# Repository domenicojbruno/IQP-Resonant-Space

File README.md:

# IQP-Resonant-Space

An interactive "resonant wall" for a hallway. VL53L0X time-of-flight sensors detect when people cross a threshold, and a honeycomb of 13 hexagonal panels, each moved by a linear actuator, pulls back from and pushes out toward them. Each actuator is driven by a BTS7960 H-bridge, and three ESP32-WROOM-32 boards each drive one row of the wall.

## System at a glance

- **Wall:** 13 motors in a flat-top hex honeycomb: 5 on top (Board A), 3 in the middle (Board B) and 5 on the bottom (Board C).
- **Motor boards:** ESP32-WROOM-32 + up to 5 BTS7960 H-bridges each, with limit switches per actuator. Position is time-based, since the actuators have no encoders.
- **Sensing:** 4× VL53L0X ToF sensors for hallway occupancy. Two overhead cameras for hand tracking are planned.
- **Master:** a PC app (Python/Tkinter) talks to the boards over **ESP-NOW** through a USB-connected ESP32 gateway. This replaced the original serial-link plan.

## Repository layout

| Path | Contents |
|---|---|
| [`firmware/ResonantWallMotorBoard/`](firmware/ResonantWallMotorBoard/) | Motor board sketch (one image for all three boards): BTS7960 drive, limit switches, time-based position, HOME/CAL/GOTO, ESP-NOW link and USB bench console |
| [`firmware/ResonantWallGateway/`](firmware/ResonantWallGateway/) | USB-serial ↔ ESP-NOW gateway sketch for the ESP32 that stays plugged into the PC |
| [`master/`](master/) | PC master app `resonant_wall_master.py` (Python/Tkinter + pyserial): wall view, threshold and GOTO-stream control, per-board links, E-STOP |
| [`docs/resonant-wall-master-spec.md`](docs/resonant-wall-master-spec.md) | Wall topology, motor addressing, actuation model and command semantics |
| [`docs/motor-board-peripheral-firmware.md`](docs/motor-board-peripheral-firmware.md) | Motor board firmware notes: ESP-NOW transport, pinout, open items |
| [`docs/master-ui-and-gateway.md`](docs/master-ui-and-gateway.md) | PC master app and ESP-NOW gateway: packet formats, line protocol, control logic |
| [`docs/vl53l0x-arduino-uno-test.md`](docs/vl53l0x-arduino-uno-test.md) | VL53L0X range test on an Arduino Uno: wiring, findings, ESP32 porting notes |
| [`docs/hexagon-node-controller.html`](docs/hexagon-node-controller.html) | Earlier node controller design sheet (Rev B): power, pin map, H-bridge wiring, sensors, BOM, layout rules |
| [`simulator/index.html`](simulator/index.html) | Resonant Wall master-node simulator. Open it in a browser and move the cursor over the hex field to see per-motor commands |
| [`docs/images/TOFpins.png`](docs/images/TOFpins.png) | VL53L0X breakout pinout |
| [`hardware/motor-driver-board/`](hardware/motor-driver-board/) | KiCad PCB (`.kicad_pcb`) and schematic PDF for the motor driver board |
| [`datasheets/`](datasheets/) | ESP32-WROOM-32, VL53L0X, BTS7960 and Arduino Uno (A000066) datasheets |

## Getting started

1. **Gateway.** Flash `firmware/ResonantWallGateway/` to a spare ESP32 and plug it into the PC. It prints `MAC <mac>` at boot.
2. **Motor boards.** In `firmware/ResonantWallMotorBoard/config.h`, set `BOARD_ID` / `MOTOR_COUNT` (0/5, 1/3, 2/5 for rows A/B/C), `USE_OLD_BENCH_PINOUT`, and `MASTER_MAC` (the gateway's MAC). Then flash each board. Each board prints its own MAC over USB at boot. The board needs Arduino-ESP32 core 3.x; the gateway builds on core 2.x or 3.x.
3. **Master.** `pip install -r master/requirements.txt`, then `python3 master/resonant_wall_master.py`. Choose the gateway port and enter each board's MAC (the app also learns a MAC from the board's first status packet). Pick a mode: Manual, Threshold (FWD/REV) or GOTO stream. Esc is E-STOP. Settings are saved to `master/resonant_wall_master.json` on exit.
4. Run `CAL` once per motor (MotorDriver Board only; it needs limit switches) so time-based positions and GOTO use the measured travel time.

## Protocol summary

| Packet | Bytes |
|---|---|
| Command (master → board) | `[0xA5, motorIdx, cmd, value]`, where `motorIdx 0xFF` means all motors |
| Status (board → master, every 250 ms) | `[0xA6, boardId, motorIdx, state, posPct, fault]` |

Command codes: FWD 0 · REV 1 · STOP 2 · HOME 3 · CAL 4 · GOTO 5. See [`docs/master-ui-and-gateway.md`](docs/master-ui-and-gateway.md) for the full tables.

## Status

- The motor driver board has been designed in KiCad but not yet fabricated. Its pinout is transcribed from the schematic and still needs to be verified against hardware.
- The VL53L0X has been bench-tested on an Arduino Uno.
- The master-node simulator (`simulator/`) runs as-is in any browser.
- The firmware and master app source is now in `firmware/` and `master/`, written from the specs in `docs/`. Neither sketch has been compiled against a real ESP32 core or run on hardware yet. Both were compiled on a host with stub headers. The motor board state machine was exercised against a simulated actuator, and the master app was tested against fake boards and a fake gateway on virtual serial ports.
- `vl53l0x_distance_test.ino` (the Uno sensor test) is not in this repo yet, and ToF occupancy is not wired into the master. The "Hallway occupied" toggle in the app stands in for it.

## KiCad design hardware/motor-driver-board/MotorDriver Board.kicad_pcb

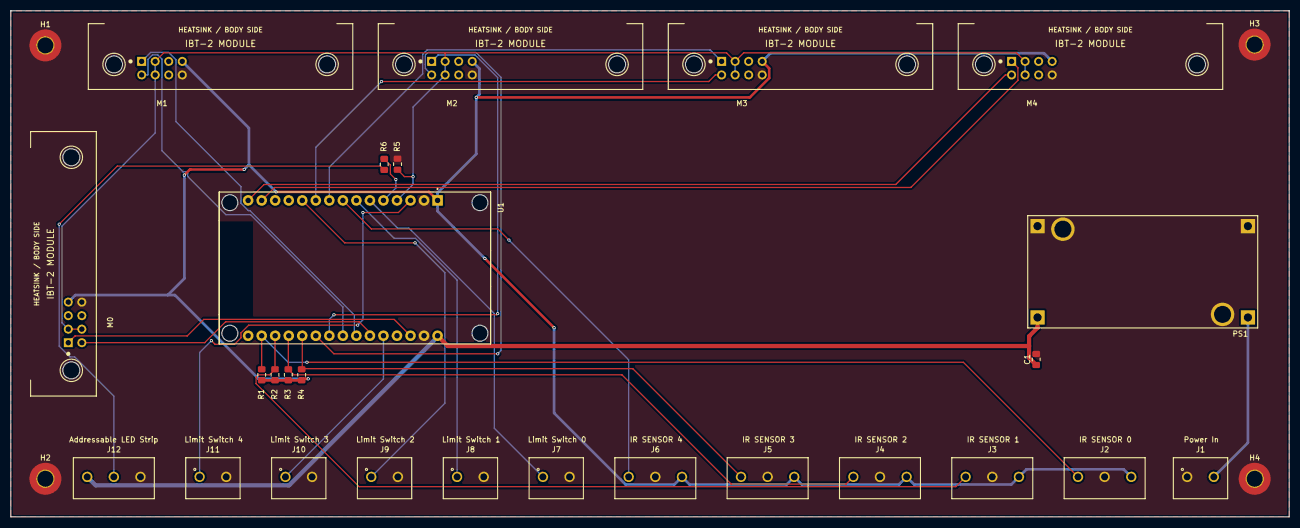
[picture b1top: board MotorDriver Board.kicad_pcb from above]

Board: 2 copper layers, 240.0 x 95.0 mm, 30 parts (0 on the bottom side), 27 nets.

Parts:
C1: 100nF; C_0805_2012Metric_Pad1.18x1.45mm_HandSolder
H1, H2, H3, H4: MountingHole_Pad; MountingHole_3mm_Pad_TopBottom
J1: Power In; 691137710002
J2: IR SENSOR 0; 691137710003
J3: IR SENSOR 1; 691137710003
J4: IR SENSOR 2; 691137710003
J5: IR SENSOR 3; 691137710003
J6: IR SENSOR 4; 691137710003
J7: Limit Switch 0; 691137710002
J8: Limit Switch 1; 691137710002
J9: Limit Switch 2; 691137710002
J10: Limit Switch 3; 691137710002
J11: Limit Switch 4; 691137710002
J12: Addressable LED Strip; 691137710003
M0, M1, M2, M3, M4: IBT-2; IBT-2_Header2x04_EdgeOverhang
PS1: MC00100; CONV_MC00100
R1, R2, R3, R4, R5: 10K; C_0805_2012Metric_Pad1.18x1.45mm_HandSolder
R6: 330; C_0805_2012Metric_Pad1.18x1.45mm_HandSolder
U1: ESP32-WROOM-32; MODULE_DEVKIT_V1_ESP32-WROOM-32

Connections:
/3.3V: J2.3, J3.3, J4.3, J5.3, J6.3, M0.7 (VCC), M1.7 (VCC), M2.7 (VCC), M3.7 (VCC), M4.7 (VCC), R1.1, R2.1, R3.1, R4.1, U1.1 (3V3)
/5V: C1.1, J12.1, PS1.OUT+, U1.30 (VIN)
/DRV_EN: M0.3 (R_EN), M0.4 (L_EN), M1.3 (R_EN), M1.4 (L_EN), M2.3 (R_EN), M2.4 (L_EN), M3.3 (R_EN), M3.4 (L_EN), M4.3 (R_EN), M4.4 (L_EN), R5.2, U1.4 (D2)
/IR0_DATA: J2.1, R1.2, U1.17 (VP)
/IR1_DATA: J3.1, R2.2, U1.18 (VN)
/IR2_DATA: J4.1, R3.2, U1.19 (D34)
/IR3_DATA: J5.1, R4.2, U1.20 (D35)
/IR4_DATA: J6.1, U1.8 (D5)
/L0_DATA: J7.1, U1.6 (RX2)
/L1_DATA: J8.1, U1.7 (TX2)
/L2_DATA: J9.1, U1.11 (D21)
/L3_DATA: J10.1, U1.26 (D14)
/L4_DATA: J11.1, U1.3 (D15)
/LED_DATA: R6.1, U1.5 (D4)
/M0_LPWM: M0.2 (LPWM), U1.25 (D27)
/M0_RPWM: M0.1 (RPWM), U1.28 (D13)
/M1_LPWM: M1.2 (LPWM), U1.23 (D25)
/M1_RPWM: M1.1 (RPWM), U1.24 (D26)
/M2_LPWM: M2.2 (LPWM), U1.21 (D32)
/M2_RPWM: M2.1 (RPWM), U1.22 (D33)
/M3_LPWM: M3.2 (LPWM), U1.10 (D19)
/M3_RPWM: M3.1 (RPWM), U1.9 (D18)
/M4_LPWM: M4.2 (LPWM), U1.15 (D23)
/M4_RPWM: M4.1 (RPWM), U1.14 (D22)
/VDD: J1.2, PS1.IN+
GND: C1.2, H1.1 (1_1), H2.1 (1_1), H3.1 (1_1), H4.1 (1_1), J1.1, J2.2, J3.2, J4.2, J5.2, J6.2, J7.2, J8.2, J9.2, J10.2, J11.2, J12.3, M0.8 (GND), M1.8 (GND), M2.8 (GND), M3.8 (GND), M4.8 (GND), PS1.IN-, PS1.MH1 (MOUTING), PS1.MH2 (MOUTING), PS1.OUT-, R5.1, U1.2 (GND), U1.29 (GND)
unnamed: J12.2, R6.2
